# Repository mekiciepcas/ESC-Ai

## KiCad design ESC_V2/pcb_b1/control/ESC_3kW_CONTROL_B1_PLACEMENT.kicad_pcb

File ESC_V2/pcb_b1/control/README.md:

# Kontrol PCB — kısmi PoC yönlendirmesi

100 × 80 mm, 4 katman; 38 elektriksel bileşen, 192 pad. 22 iz segmenti, 120 açık bağlantı, mevcut kurallarla DRC 0 ihlal. C1801–C1804 dijital bypass çiftleri MCU pinlerine bağlı. VBAT, analog besleme ve ortak güç/GND dağıtımı tamamlanmadı. Üretim veya enerji verme onayı değildir.

Kaynak: ESC_3kW_CONTROL_B1_PLACEMENT.kicad_pcb. Kanıt: supply_routes_20260915.json ve drc_placement.json. Değişiklik öncesi snapshot korunur. route/refine betikleri tarihsel tek seferlik değişikliklerdir; mevcut PCB üzerine yeniden uygulanmaz. Aday kılıflar placement_report.json içinde açıkça işaretlidir.

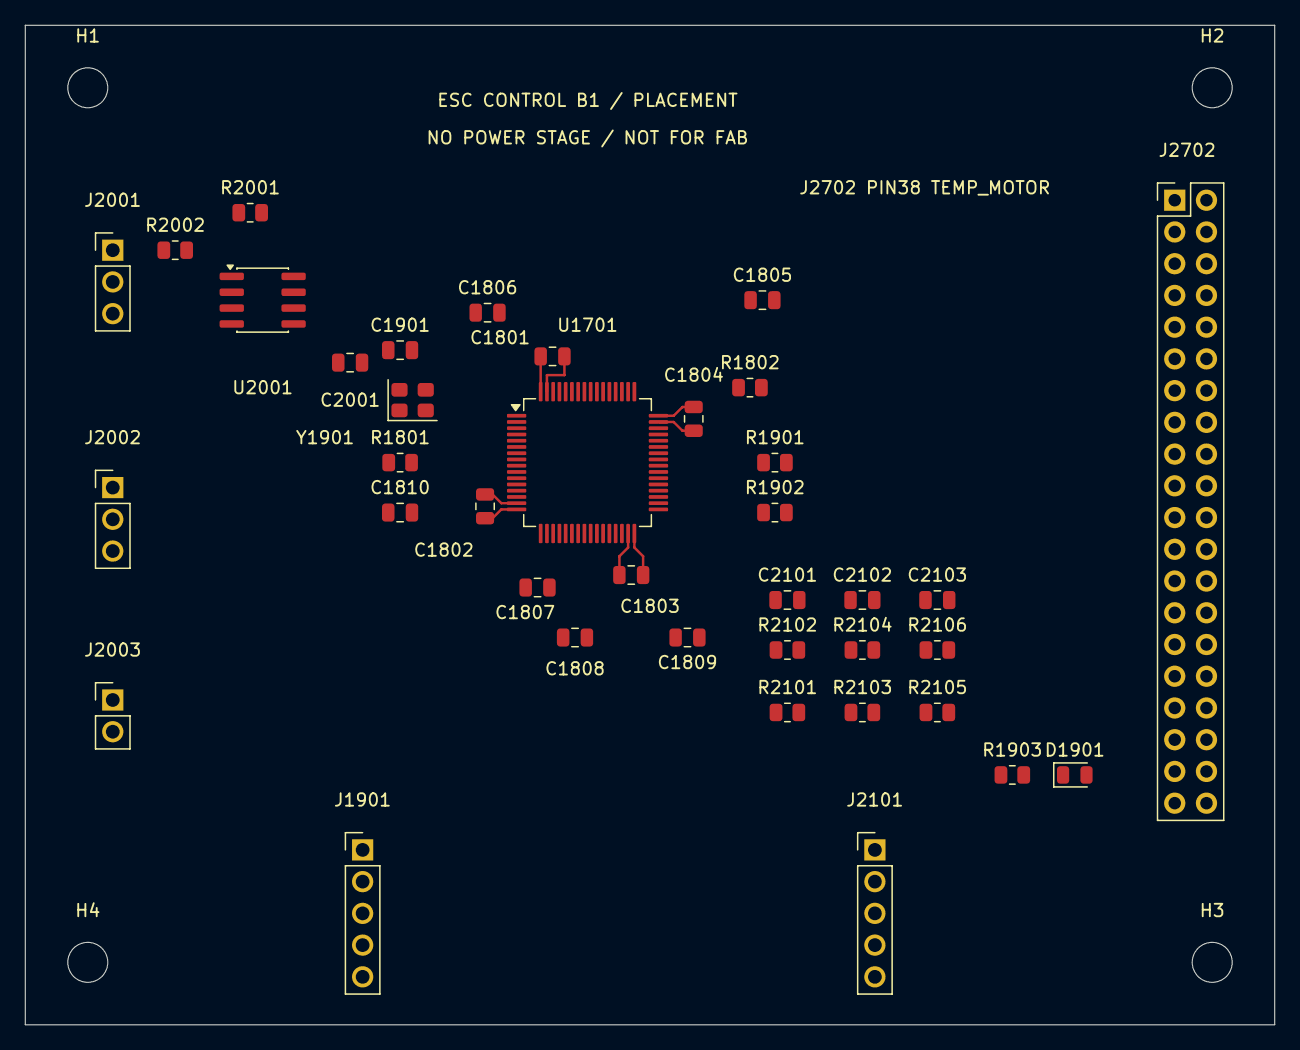
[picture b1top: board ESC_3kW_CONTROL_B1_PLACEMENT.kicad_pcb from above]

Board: 4 copper layers, 100.0 x 80.0 mm, 42 parts (0 on the bottom side), 52 nets.

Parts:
C1801, C1802, C1803, C1804: 100n at VDD; C_0805_2012Metric
C1805: 4.7u; C_0805_2012Metric
C1806: 100n at VBAT; C_0805_2012Metric
C1807: 1u VDDA; C_0805_2012Metric
C1808: 100n VDDA; C_0805_2012Metric
C1809: 100n VREF; C_0805_2012Metric
C1810: 100n reset; C_0805_2012Metric
C1901: 100n oscillator; C_0805_2012Metric
C2001: 100n CAN; C_0805_2012Metric
C2101, C2102, C2103: 1n; C_0805_2012Metric
D1901: LED GREEN; LED_0805_2012Metric
H1, H2, H3, H4: MountingHole_3.2mm_M3
J1901: SWD; WE_61300511121_1x05_P2.54_Drill1.10
J2001: CAN; WE_61300311121_1x03_P2.54_Drill1.10
J2002: UART 3V3; WE_61300311121_1x03_P2.54_Drill1.10
J2003: RC PWM 3V3; WE_61300211121_1x02_P2.54_Drill1.10
J2101: HALL 5V; WE_61300511121_1x05_P2.54_Drill1.10
J2702: CONTROL CARD 2x20; PinHeader_2x20_P2.54mm_Vertical
R1801, R1901, R1902: 10k; R_0805_2012Metric
R1802: 10k BOOT0; R_0805_2012Metric
R1903: 1k LED; R_0805_2012Metric
R2001: 10k slope; R_0805_2012Metric
R2002: 120R DNP; R_0805_2012Metric
R2101, R2103, R2105: 4.7k 3V3 pull-up; R_0805_2012Metric
R2102, R2104, R2106: 1k; R_0805_2012Metric
U1701: STM32G474RET3; LQFP-64_10x10mm_P0.5mm
U2001: SN65HVD230DR; SOIC-8_3.9x4.9mm_P1.27mm
Y1901: 8MHz 3V3 CMOS oscillator; Oscillator_SMD_Abracon_ASE-4Pin_3.2x2.5mm

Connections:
+3V3: C1801.1, C1802.1, C1803.1, C1804.1, C1805.1, C1806.1, C1901.1, C2001.1, J1901.1, J2702.2, R1801.2, R1903.1, R2101.1, R2103.1, R2105.1, U1701.1, U1701.16, U1701.32, U1701.48, U1701.64, U2001.3, Y1901.1, Y1901.4
+3V3A: C1807.1, C1808.1, C1809.1, J2702.4, U1701.28, U1701.29
+5V: J2101.1, J2702.39
ARM_CLK: J2702.15, R1901.1, U1701.23
BOOT0: R1802.1, U1701.61
CAN_H: J2001.2, R2002.1, U2001.7
CAN_L: J2001.3, R2002.2, U2001.6
CAN_RS: R2001.1, U2001.8
CAN_RX: U1701.45, U2001.4
CAN_TX: U1701.46, U2001.1
DRV_CS_N: J2702.19, U1701.22
DRV_FAULT_N: J2702.18, U1701.33
GND: C1801.2, C1802.2, C1803.2, C1804.2, C1805.2, C1806.2, C1807.2, C1808.2, C1809.2, C1810.2, C1901.2, C2001.2, C2101.2, C2102.2, C2103.2, J1901.3, J2001.1, J2002.1, J2003.1, J2101.2, J2702.1, J2702.3, J2702.7, J2702.10, J2702.13, J2702.23, J2702.27, J2702.32, J2702.40, R1802.2, R1901.2, R1902.2, R2001.2, U1701.15, U1701.27, U1701.31, U1701.47, U1701.63, U2001.2, Y1901.2
HALL_A: C2101.1, R2102.2, U1701.38
HALL_A_EXT: J2101.3, R2101.2, R2102.1
HALL_B: C2102.1, R2104.2, U1701.39
HALL_B_EXT: J2101.4, R2103.2, R2104.1
HALL_C: C2103.1, R2106.2, U1701.40
HALL_C_EXT: J2101.5, R2105.2, R2106.1
HARD_FAULT_N: J2702.17, U1701.34
HSE_IN: U1701.5, Y1901.3
I_A_ADC: J2702.24, U1701.12
I_B_ADC: J2702.25, U1701.13
I_C_ADC: J2702.26, U1701.14
LATCH_STATE: J2702.16, U1701.55
LED_A: D1901.2, R1903.2
MCU_PWM_HA: J2702.5, U1701.42
MCU_PWM_HB: J2702.8, U1701.43
MCU_PWM_HC: J2702.11, U1701.44
MCU_PWM_LA: J2702.6, U1701.35
MCU_PWM_LB: J2702.9, U1701.36
MCU_PWM_LC: J2702.12, U1701.37
NRST: C1810.1, J1901.5, J2702.37, R1801.1, U1701.7
PG_5V: J2702.36, U1701.30
PG_12V: J2702.35, U1701.26
RC_PWM: J2003.2, U1701.51
RUN_REQUEST: J2702.14, R1902.1, U1701.41
SPI_MISO: J2702.22, U1701.57
SPI_MOSI: J2702.21, U1701.58
SPI_SCK: J2702.20, U1701.56
STATUS_LED: D1901.1, U1701.54
SWCLK: J1901.4, U1701.50
SWDIO: J1901.2, U1701.49
TEMP_FET: J2702.33, U1701.17
TEMP_MOTOR: J2702.38, U1701.24
TEMP_PCB: J2702.34, U1701.18
UART_RX: J2002.2, U1701.53
UART_TX: J2002.3, U1701.52
V_A_ADC: J2702.29, U1701.9
V_BUS_ADC: J2702.28, U1701.8
V_B_ADC: J2702.30, U1701.10
V_C_ADC: J2702.31, U1701.11
